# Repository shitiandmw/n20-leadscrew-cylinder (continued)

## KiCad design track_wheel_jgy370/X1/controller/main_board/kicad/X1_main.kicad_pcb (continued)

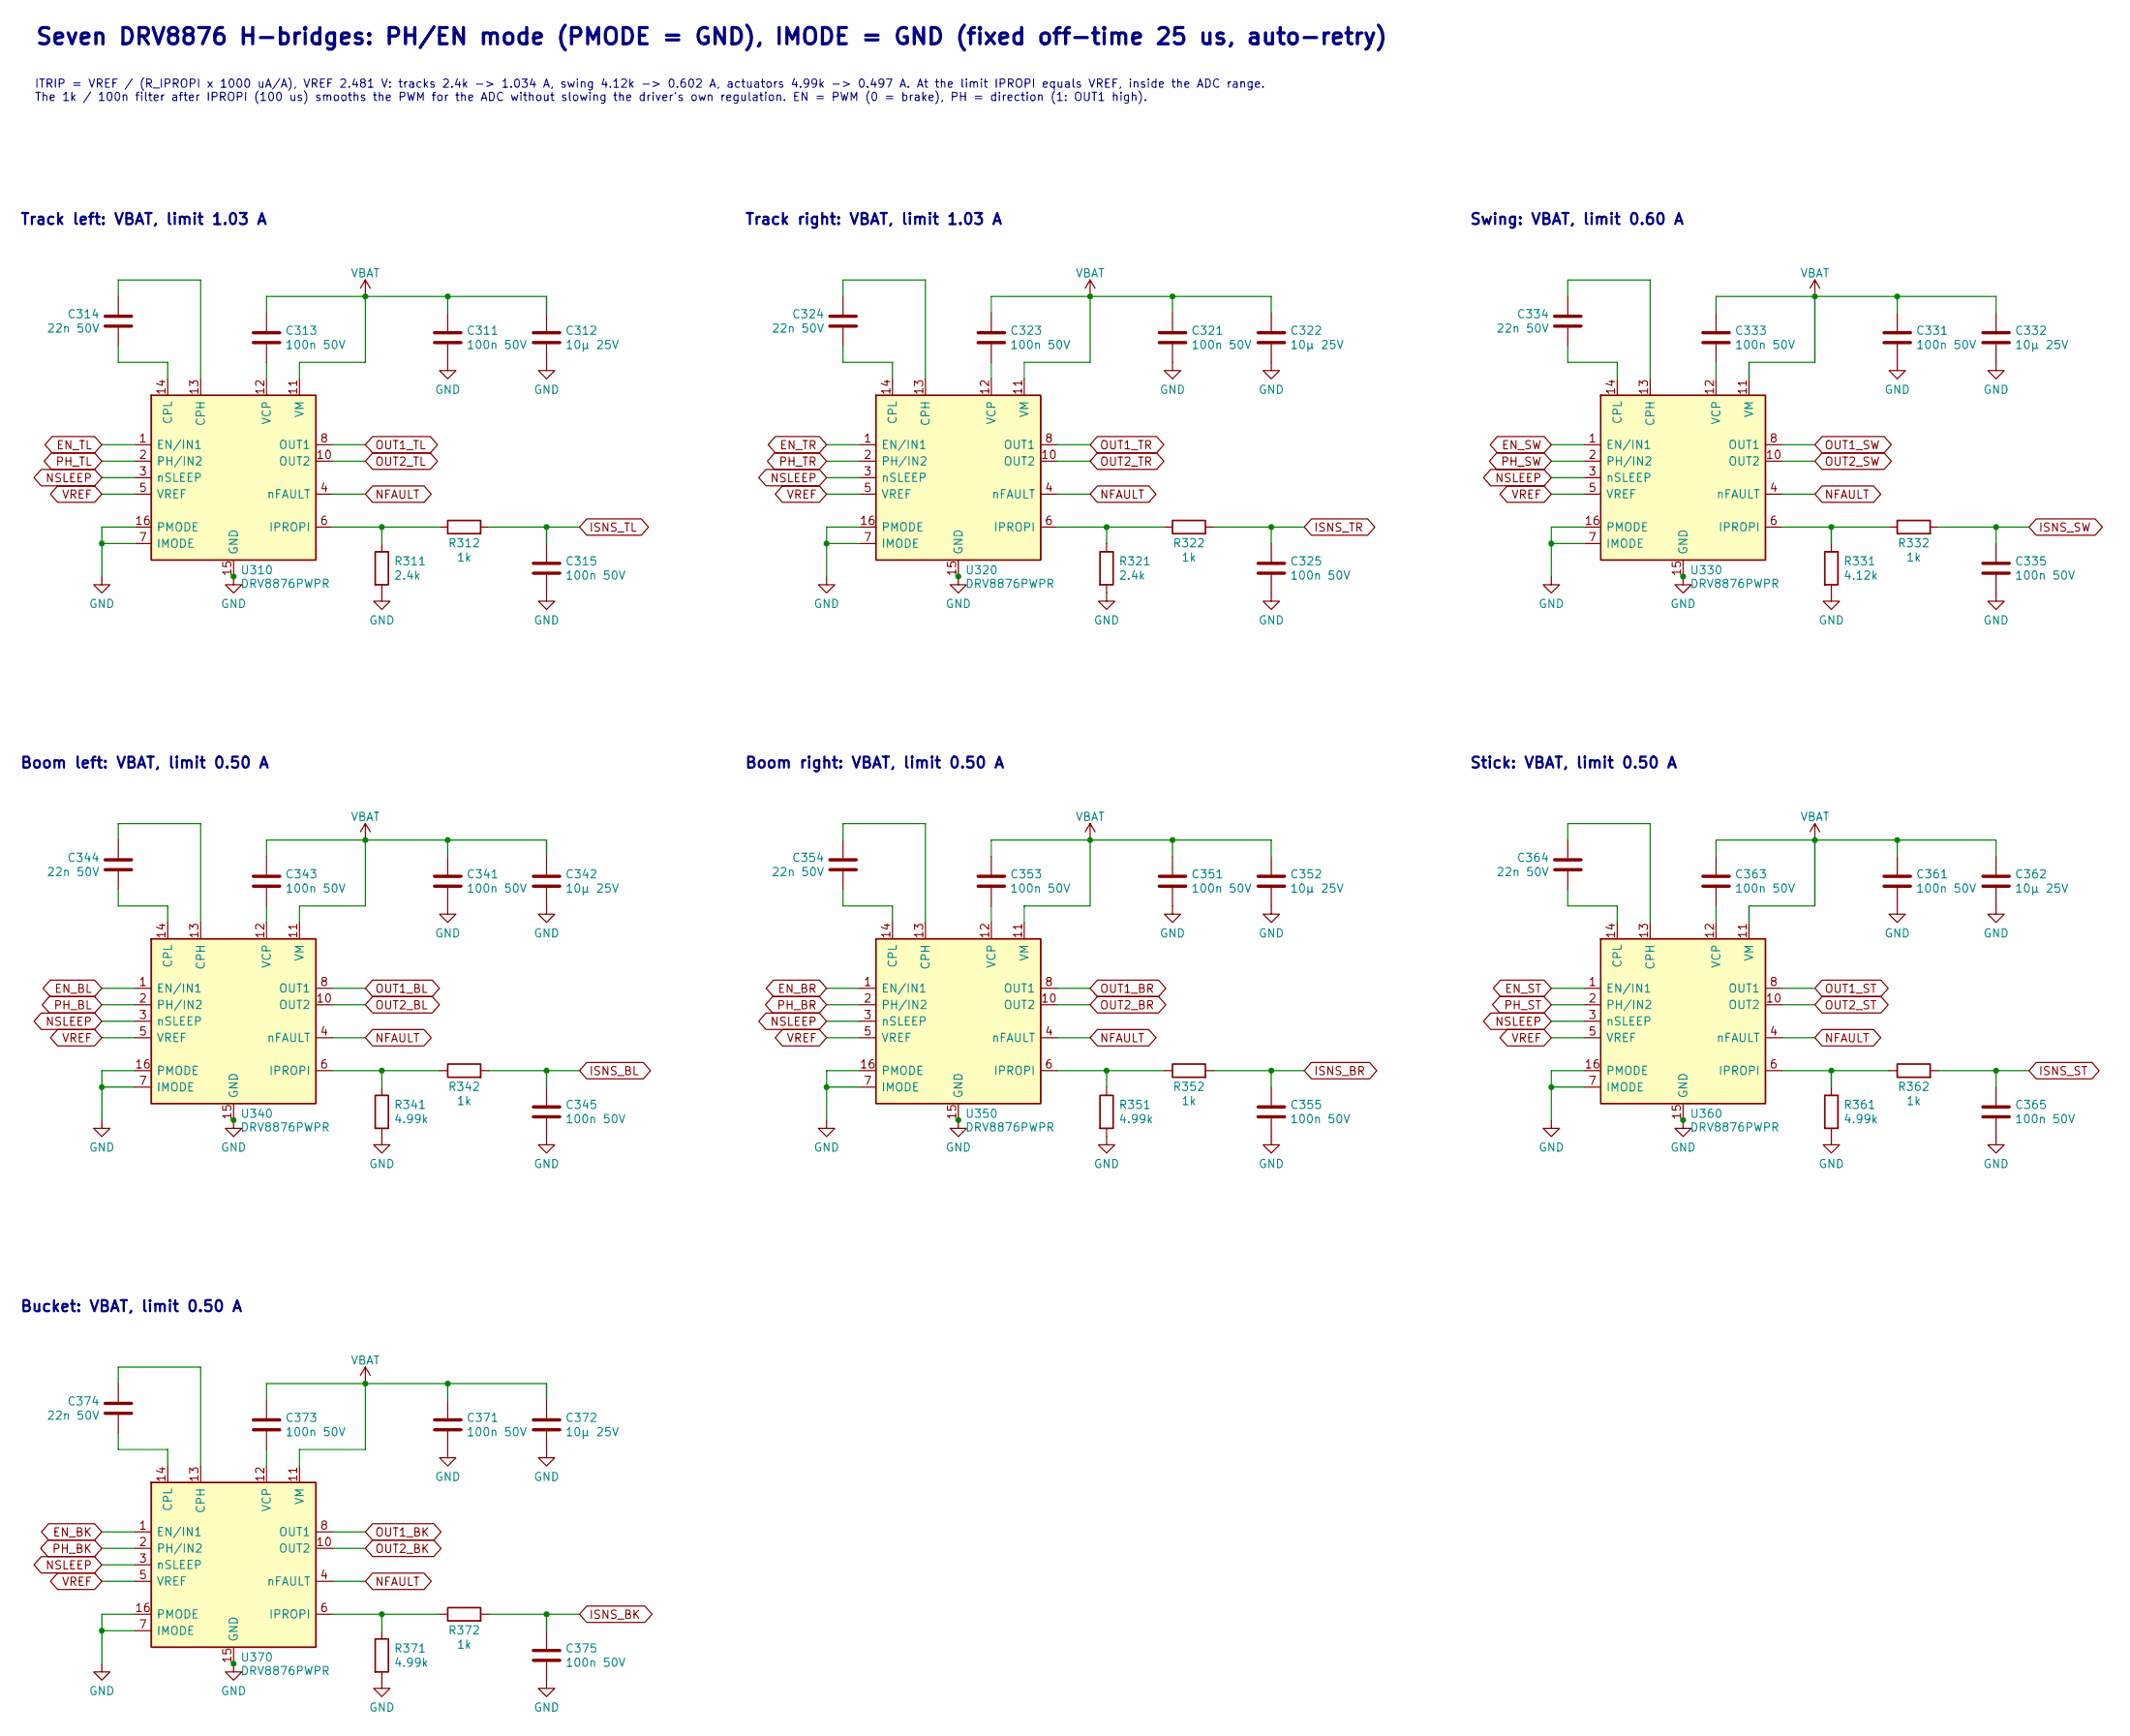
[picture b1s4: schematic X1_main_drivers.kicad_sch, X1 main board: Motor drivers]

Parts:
C311, C313, C315, C321, C323, C325, C331, C333, C335, C341, C343, C345, C351, C353, C355, C361, C363, C365, C371, C373, C375: 100n 50V; C_0603_1608Metric; MPN Yageo CC0603KRX7R9BB104; LCSC C14663
C312, C322, C332, C342, C352, C362, C372: 10µ 25V; C_0805_2012Metric; MPN Samsung CL21A106KAYNNNE; LCSC C15850
C314, C324, C334, C344, C354, C364, C374: 22n 50V; C_0603_1608Metric; MPN Samsung CL10B223KB8NNNC; LCSC C21122
R311, R321: 2.4k; R_0603_1608Metric; MPN UNI-ROYAL 0603WAF, 2.4k 1 %; LCSC C22940
R312, R322, R332, R342, R352, R362, R372: 1k; R_0603_1608Metric; MPN UNI-ROYAL 0603WAF, 1k 1 %; LCSC C21190
R331: 4.12k; R_0603_1608Metric; MPN UNI-ROYAL 0603WAF, 4.12k 1 %; LCSC C23041
R341, R351, R361, R371: 4.99k; R_0603_1608Metric; MPN UNI-ROYAL 0603WAF, 4.99k 1 %; LCSC C23046
U310, U320, U330, U340, U350, U360, U370: DRV8876PWPR; HTSSOP-16-1EP_4.4x5mm_P0.65mm_EP3.4x5mm_Mask2.46x2.31mm_The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; MPN TI DRV8876PWPR; LCSC C575551

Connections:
EN_BK: U370.1 (EN/IN1); also elsewhere on the board
EN_BL: U340.1 (EN/IN1); also elsewhere on the board
EN_BR: U350.1 (EN/IN1); also elsewhere on the board
EN_ST: U360.1 (EN/IN1); also elsewhere on the board
EN_SW: U330.1 (EN/IN1); also elsewhere on the board
EN_TL: U310.1 (EN/IN1); also elsewhere on the board
EN_TR: U320.1 (EN/IN1); also elsewhere on the board
GND: C311.2, C312.2, C315.2, C321.2, C322.2, C325.2, C331.2, C332.2, C335.2, C341.2, C342.2, C345.2, C351.2, C352.2, C355.2, C361.2, C362.2, C365.2, C371.2, C372.2, C375.2, R311.2, R321.2, R331.2, R341.2, R351.2, R361.2, R371.2, U310.7 (IMODE), U310.9 (PGND), U310.15 (GND), U310.16 (PMODE), U310.17 (PAD), U320.7 (IMODE), U320.9 (PGND), U320.15 (GND), U320.16 (PMODE), U320.17 (PAD), U330.7 (IMODE), U330.9 (PGND), U330.15 (GND), U330.16 (PMODE), U330.17 (PAD), U340.7 (IMODE), U340.9 (PGND), U340.15 (GND), U340.16 (PMODE), U340.17 (PAD), U350.7 (IMODE), U350.9 (PGND), U350.15 (GND), U350.16 (PMODE), U350.17 (PAD), U360.7 (IMODE), U360.9 (PGND), U360.15 (GND), U360.16 (PMODE), U360.17 (PAD), U370.7 (IMODE), U370.9 (PGND), U370.15 (GND), U370.16 (PMODE), U370.17 (PAD); also elsewhere on the board
ISNS_BK: C375.1, R372.2; also elsewhere on the board
ISNS_BL: C345.1, R342.2; also elsewhere on the board
ISNS_BR: C355.1, R352.2; also elsewhere on the board
ISNS_ST: C365.1, R362.2; also elsewhere on the board
ISNS_SW: C335.1, R332.2; also elsewhere on the board
ISNS_TL: C315.1, R312.2; also elsewhere on the board
ISNS_TR: C325.1, R322.2; also elsewhere on the board
NFAULT: U310.4 (nFAULT), U320.4 (nFAULT), U330.4 (nFAULT), U340.4 (nFAULT), U350.4 (nFAULT), U360.4 (nFAULT), U370.4 (nFAULT); also elsewhere on the board
NSLEEP: U310.3 (nSLEEP), U320.3 (nSLEEP), U330.3 (nSLEEP), U340.3 (nSLEEP), U350.3 (nSLEEP), U360.3 (nSLEEP), U370.3 (nSLEEP); also elsewhere on the board
unnamed: C314.1, U310.13 (CPH)
unnamed: C314.2, U310.14 (CPL)
unnamed: R311.1, R312.1, U310.6 (IPROPI)
unnamed: C313.1, U310.12 (VCP)
unnamed: C324.1, U320.13 (CPH)
unnamed: C324.2, U320.14 (CPL)
unnamed: R321.1, R322.1, U320.6 (IPROPI)
unnamed: C323.1, U320.12 (VCP)
unnamed: C334.1, U330.13 (CPH)
unnamed: C334.2, U330.14 (CPL)
unnamed: R331.1, R332.1, U330.6 (IPROPI)
unnamed: C333.1, U330.12 (VCP)
unnamed: C344.1, U340.13 (CPH)
unnamed: C344.2, U340.14 (CPL)
unnamed: R341.1, R342.1, U340.6 (IPROPI)
unnamed: C343.1, U340.12 (VCP)
unnamed: C354.1, U350.13 (CPH)
unnamed: C354.2, U350.14 (CPL)
unnamed: R351.1, R352.1, U350.6 (IPROPI)
unnamed: C353.1, U350.12 (VCP)
unnamed: C364.1, U360.13 (CPH)
unnamed: C364.2, U360.14 (CPL)
unnamed: R361.1, R362.1, U360.6 (IPROPI)
unnamed: C363.1, U360.12 (VCP)
unnamed: C374.1, U370.13 (CPH)
unnamed: C374.2, U370.14 (CPL)
unnamed: R371.1, R372.1, U370.6 (IPROPI)
unnamed: C373.1, U370.12 (VCP)
OUT1_BK: U370.8 (OUT1); also elsewhere on the board
OUT1_BL: U340.8 (OUT1); also elsewhere on the board
OUT1_BR: U350.8 (OUT1); also elsewhere on the board
OUT1_ST: U360.8 (OUT1); also elsewhere on the board
OUT1_SW: U330.8 (OUT1); also elsewhere on the board
OUT1_TL: U310.8 (OUT1); also elsewhere on the board
OUT1_TR: U320.8 (OUT1); also elsewhere on the board
OUT2_BK: U370.10 (OUT2); also elsewhere on the board
OUT2_BL: U340.10 (OUT2); also elsewhere on the board
OUT2_BR: U350.10 (OUT2); also elsewhere on the board
OUT2_ST: U360.10 (OUT2); also elsewhere on the board
OUT2_SW: U330.10 (OUT2); also elsewhere on the board
OUT2_TL: U310.10 (OUT2); also elsewhere on the board
OUT2_TR: U320.10 (OUT2); also elsewhere on the board
PH_BK: U370.2 (PH/IN2); also elsewhere on the board
PH_BL: U340.2 (PH/IN2); also elsewhere on the board
PH_BR: U350.2 (PH/IN2); also elsewhere on the board
PH_ST: U360.2 (PH/IN2); also elsewhere on the board
PH_SW: U330.2 (PH/IN2); also elsewhere on the board
PH_TL: U310.2 (PH/IN2); also elsewhere on the board
PH_TR: U320.2 (PH/IN2); also elsewhere on the board
VBAT: C311.1, C312.1, C313.2, C321.1, C322.1, C323.2, C331.1, C332.1, C333.2, C341.1, C342.1, C343.2, C351.1, C352.1, C353.2, C361.1, C362.1, C363.2, C371.1, C372.1, C373.2, U310.11 (VM), U320.11 (VM), U330.11 (VM), U340.11 (VM), U350.11 (VM), U360.11 (VM), U370.11 (VM); also elsewhere on the board
VREF: U310.5 (VREF), U320.5 (VREF), U330.5 (VREF), U340.5 (VREF), U350.5 (VREF), U360.5 (VREF), U370.5 (VREF); also elsewhere on the board

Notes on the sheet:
Seven DRV8876 H-bridges: PH/EN mode (PMODE = GND), IMODE = GND (fixed off-time 25 us, auto-retry)
ITRIP = VREF / (R_IPROPI x 1000 uA/A), VREF 2.481 V: tracks 2.4k -> 1.034 A, swing 4.12k -> 0.602 A, actuators 4.99k -> 0.497 A. At the limit IPROPI equals VREF, inside the ADC range. The 1k / 100n filter after IPROPI (100 us) smooths the PWM for the ADC without slowing the driver's own regulation.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
Track left: VBAT, limit 1.03 A
Track right: VBAT, limit 1.03 A
Swing: VBAT, limit 0.60 A
Boom left: VBAT, limit 0.50 A
Boom right: VBAT, limit 0.50 A
Stick: VBAT, limit 0.50 A
Bucket: VBAT, limit 0.50 A

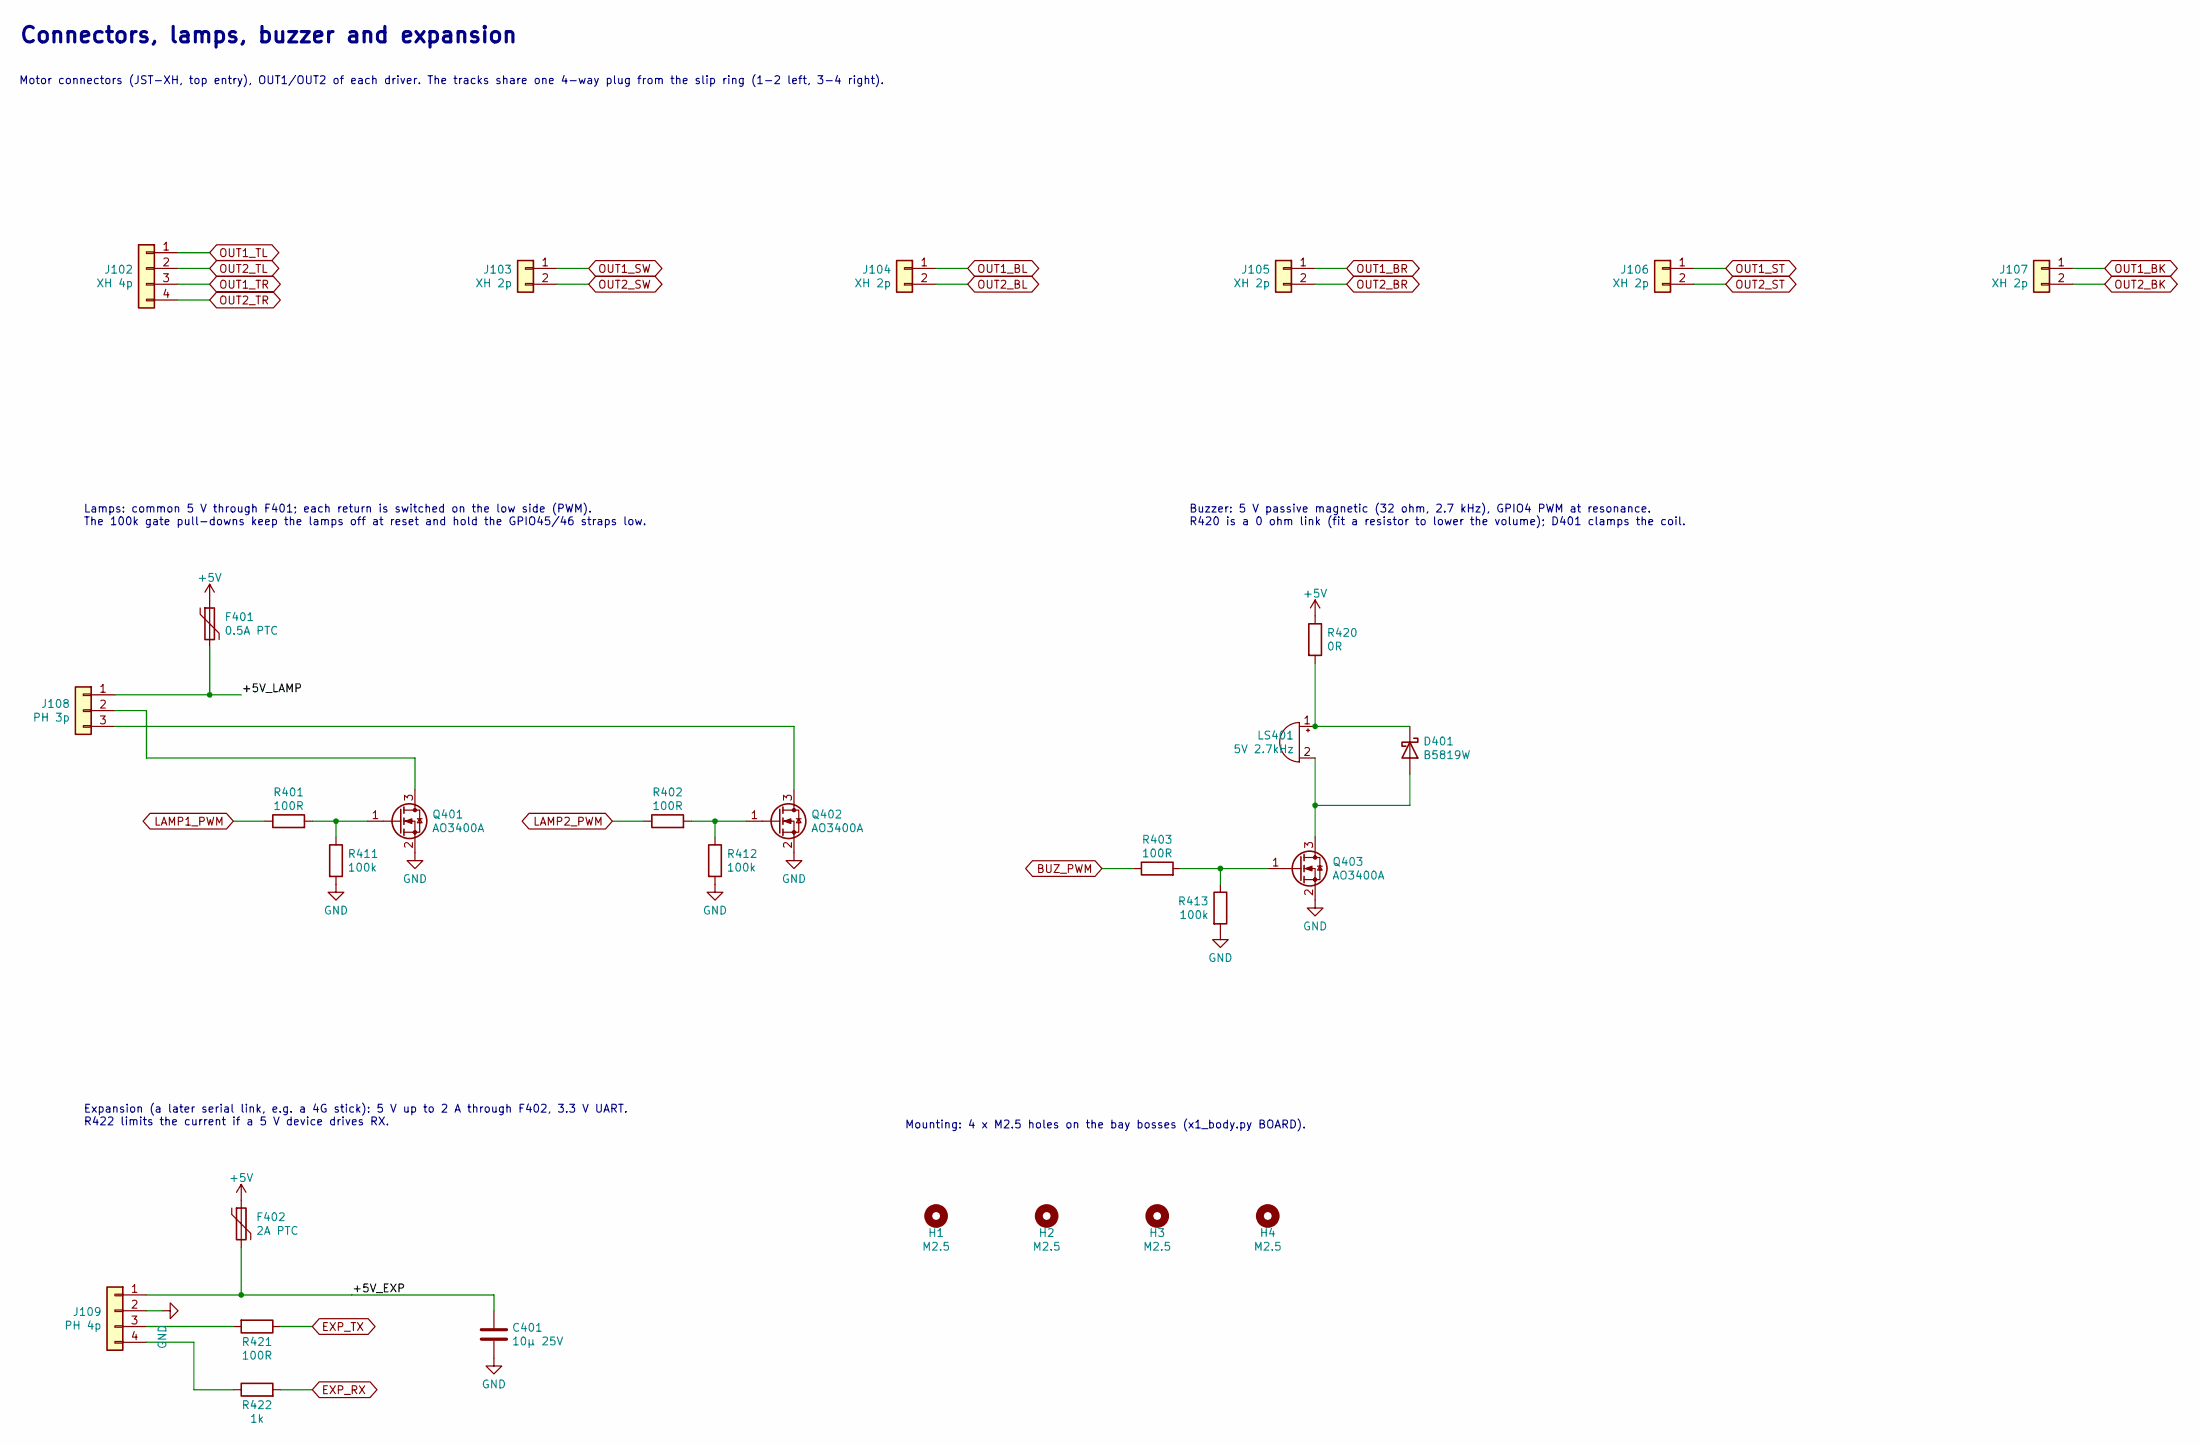
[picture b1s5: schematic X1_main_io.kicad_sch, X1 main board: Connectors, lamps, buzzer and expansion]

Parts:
C401: 10µ 25V; C_0805_2012Metric; MPN Samsung CL21A106KAYNNNE; LCSC C15850
D401: B5819W; D_SOD-123; MPN JSCJ B5819W SL; LCSC C8598
F401: 0.5A PTC; Fuse_1206_3216Metric; MPN BHFUSE BSMD1206-050-16V; LCSC C883124
F402: 2A PTC; Fuse_1812_4532Metric; MPN BHFUSE BSMD1812-200-16V; LCSC C883156
H1, H2, H3, H4: M2.5; MountingHole_2.7mm_M2.5; MPN mounting hole
J102: XH 4p; JST_XH_B4B-XH-A_1x04_P2.50mm_Vertical; MPN JST B4B-XH-A(LF)(SN); LCSC C144395
J103, J104, J105, J106, J107: XH 2p; JST_XH_B2B-XH-A_1x02_P2.50mm_Vertical; MPN JST B2B-XH-A(LF)(SN); LCSC C158012
J108: PH 3p; JST_PH_B3B-PH-K_1x03_P2.00mm_Vertical; MPN JST B3B-PH-K-S(LF)(SN); LCSC C131339
J109: PH 4p; JST_PH_B4B-PH-K_1x04_P2.00mm_Vertical; MPN JST B4B-PH-K-S(LF)(SN); LCSC C131334
LS401: 5V 2.7kHz; Buzzer_XHXDZ_8530; MPN XHXDZ SMD8530-32Ω (5 V passive, 32 Ω); LCSC C49246949
Q401, Q402, Q403: AO3400A; SOT-23; MPN AOS AO3400A; LCSC C20917
R401, R402, R403, R421: 100R; R_0603_1608Metric; MPN UNI-ROYAL 0603WAF, 100R 1 %; LCSC C22775
R411, R412, R413: 100k; R_0603_1608Metric; MPN UNI-ROYAL 0603WAF, 100k 1 %; LCSC C25803
R420: 0R; R_0603_1608Metric; MPN UNI-ROYAL 0603WAF, 0R 1 %; LCSC C21189
R422: 1k; R_0603_1608Metric; MPN UNI-ROYAL 0603WAF, 1k 1 %; LCSC C21190

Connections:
+5V: F401.1, F402.1, R420.1; also elsewhere on the board
/Connectors, lamps, buzzer and expansion/+5V_EXP: C401.1, F402.2, J109.1
/Connectors, lamps, buzzer and expansion/+5V_LAMP: F401.2, J108.1
BUZ_PWM: R403.1; also elsewhere on the board
EXP_RX: R422.2; also elsewhere on the board
EXP_TX: R421.1; also elsewhere on the board
GND: C401.2, J109.2, Q401.2 (S), Q402.2 (S), Q403.2 (S), R411.2, R412.2, R413.2; also elsewhere on the board
LAMP1_PWM: R401.1; also elsewhere on the board
LAMP2_PWM: R402.1; also elsewhere on the board
unnamed: D401.2 (A), LS401.2 (-), Q403.3 (D)
unnamed: D401.1 (K), LS401.1 (+), R420.2
unnamed: J108.2, Q401.3 (D)
unnamed: J108.3, Q402.3 (D)
unnamed: J109.3, R421.2
unnamed: J109.4, R422.1
unnamed: Q401.1 (G), R401.2, R411.1
unnamed: Q402.1 (G), R402.2, R412.1
unnamed: Q403.1 (G), R403.2, R413.1
OUT1_BK: J107.1; also elsewhere on the board
OUT1_BL: J104.1; also elsewhere on the board
OUT1_BR: J105.1; also elsewhere on the board
OUT1_ST: J106.1; also elsewhere on the board
OUT1_SW: J103.1; also elsewhere on the board
OUT1_TL: J102.1; also elsewhere on the board
OUT1_TR: J102.3; also elsewhere on the board
OUT2_BK: J107.2; also elsewhere on the board
OUT2_BL: J104.2; also elsewhere on the board
OUT2_BR: J105.2; also elsewhere on the board
OUT2_ST: J106.2; also elsewhere on the board
OUT2_SW: J103.2; also elsewhere on the board
OUT2_TL: J102.2; also elsewhere on the board
OUT2_TR: J102.4; also elsewhere on the board

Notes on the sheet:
Connectors, lamps, buzzer and expansion
Motor connectors (JST-XH, top entry), OUT1/OUT2 of each driver. The tracks share one 4-way plug from the slip ring (1-2 left, 3-4 right).
Lamps: common 5 V through F401; each return is switched on the low side (PWM). The 100k gate pull-downs keep the lamps off at reset and hold the GPIO45/46 straps low.
Buzzer: 5 V passive magnetic (32 ohm, 2.7 kHz), GPIO4 PWM at resonance. R420 is a 0 ohm link (fit a resistor to lower the volume); D401 clamps the coil.
Expansion (a later serial link, e.g. a 4G stick): 5 V up to 2 A through F402, 3.3 V UART. R422 limits the current if a 5 V device drives RX.
Mounting: 4 x M2.5 holes on the bay bosses (x1_body.py BOARD).

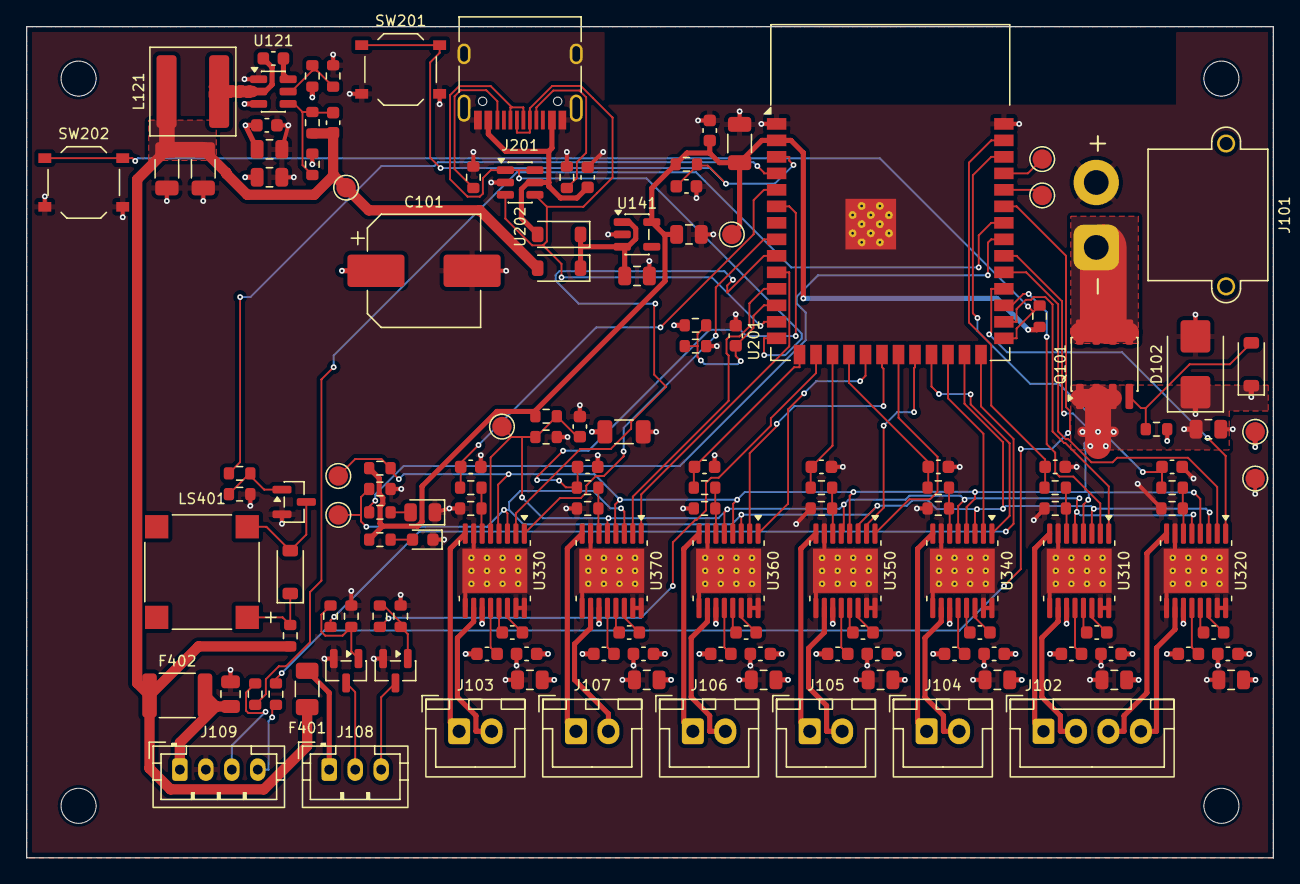
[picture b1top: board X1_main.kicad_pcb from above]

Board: 4 copper layers, 96.0 x 64.0 mm, 145 parts (0 on the bottom side), 106 nets.

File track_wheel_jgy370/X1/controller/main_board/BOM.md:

# X1 main board rev B: bill of materials

Generated by `source/bom.py` from `source/netlist.py`; do not edit by hand.

- 42 lines and 132 placed parts per board. Test pads and mounting holes are copper only.
- **JLCPCB library type:** 19 lines are Basic, 1 are Preferred Extended, and 22 are Extended, which carry a per-part loading fee.
- The library type, part numbers and ratings were checked on LCSC and JLCPCB on 2026-11-05 (sources in DESIGN.md).

| Designators | Qty | Value | Part | Footprint | LCSC | JLC library | Height mm |
|---|---|---|---|---|---|---|---|
| C101 | 1 | 220µ 35V | Nichicon UCD1V221MNL1GS | `CP_Elec_8x10.5` | C136294 | Extended | 10.5 |
| C102, C121, C122, C141, C142, C312, C322, C332, C342, C352, C362, C372, C401 | 13 | 10µ 25V | Samsung CL21A106KAYNNNE | `C_0805_2012Metric` | C15850 | Basic | 1.25 |
| C103, C123, C124, C151, C202, C311, C313, C315, C321, C323, C325, C331, C333, C335, C341, C343, C345, C351, C353, C355, C361, C363, C365, C371, C373, C375 | 26 | 100n 50V | Yageo CC0603KRX7R9BB104 | `C_0603_1608Metric` | C14663 | Basic | 0.9 |
| C125, C126, C130, C201 | 4 | 22µ 25V | Samsung CL31A226KAHNNNE | `C_1206_3216Metric` | C12891 | Basic | 1.6 |
| C127 | 1 | 68p C0G | Samsung CL10C680JB8NNNC | `C_0603_1608Metric` | C28262 | Preferred ext. | 0.9 |
| C203, C204 | 2 | 1µ 50V | Samsung CL10A105KB8NNNC | `C_0603_1608Metric` | C15849 | Basic | 0.9 |
| C314, C324, C334, C344, C354, C364, C374 | 7 | 22n 50V | Samsung CL10B223KB8NNNC | `C_0603_1608Metric` | C21122 | Basic | 0.9 |
| D101 | 1 | BZT52C12 | JSCJ BZT52C12 | `D_SOD-123` | C43491 | Extended | 1.35 |
| D102 | 1 | SMBJ15A | Littelfuse SMBJ15A (unidirectional) | `D_SMB` | C83846 | Extended | 2.3 |
| D141, D142, D401 | 3 | B5819W | JSCJ B5819W SL | `D_SOD-123` | C8598 | Basic | 1.35 |
| D201 | 1 | green | Hubei KENTO KT-0805G | `LED_0805_2012Metric` | C2297 | Basic | 0.8 |
| D202 | 1 | red | Hubei KENTO KT-0603R | `LED_0603_1608Metric` | C2286 | Basic | 0.8 |
| F401 | 1 | 0.5A PTC | BHFUSE BSMD1206-050-16V | `Fuse_1206_3216Metric` | C883124 | Extended | 1 |
| F402 | 1 | 2A PTC | BHFUSE BSMD1812-200-16V | `Fuse_1812_4532Metric` | C883156 | Extended | 1 |
| J101 | 1 | XT30PW-M | Amass XT30PW-M30.G.Y | `AMASS_XT30PW-M_1x02_P2.50mm_Horizontal` | C431092 | Extended | 5.2 |
| J102 | 1 | XH 4p | JST B4B-XH-A(LF)(SN) | `JST_XH_B4B-XH-A_1x04_P2.50mm_Vertical` | C144395 | Extended | 7 |
| J103, J104, J105, J106, J107 | 5 | XH 2p | JST B2B-XH-A(LF)(SN) | `JST_XH_B2B-XH-A_1x02_P2.50mm_Vertical` | C158012 | Extended | 7 |
| J108 | 1 | PH 3p | JST B3B-PH-K-S(LF)(SN) | `JST_PH_B3B-PH-K_1x03_P2.00mm_Vertical` | C131339 | Extended | 6 |
| J109 | 1 | PH 4p | JST B4B-PH-K-S(LF)(SN) | `JST_PH_B4B-PH-K_1x04_P2.00mm_Vertical` | C131334 | Extended | 6 |
| J201 | 1 | USB-C | Korean Hroparts TYPE-C-31-M-12 | `USB_C_Receptacle_HRO_TYPE-C-31-M-12` | C165948 | Extended | 3.26 |
| L121 | 1 | 10µH | Bourns SRP6060FA-100M | `L_Bourns_SRP6060FA` | C2046759 | Extended | 6 |
| LS401 | 1 | 5V 2.7kHz | XHXDZ SMD8530-32Ω (5 V passive, 32 Ω) | `Buzzer_XHXDZ_8530` | C49246949 | Extended | 3 |
| Q101 | 1 | AO4407A | AOS AO4407A | `SOIC-8_3.9x4.9mm_P1.27mm` | C16072 | Extended | 1.75 |
| Q401, Q402, Q403 | 3 | AO3400A | AOS AO3400A | `SOT-23` | C20917 | Extended | 1.25 |
| R101, R102, R121, R123, R208, R411, R412, R413 | 8 | 100k | UNI-ROYAL 0603WAF, 100k 1 % | `R_0603_1608Metric` | C25803 | Basic | 0.5 |
| R103, R124 | 2 | 22k | UNI-ROYAL 0603WAF, 22k 1 % | `R_0603_1608Metric` | C31850 | Basic | 0.5 |
| R122 | 1 | 13.3k | UNI-ROYAL 0603WAF, 13.3k 1 % | `R_0603_1608Metric` | C25952 | Extended | 0.5 |
| R151 | 1 | 3.3k | UNI-ROYAL 0603WAF, 3.3k 1 % | `R_0603_1608Metric` | C22978 | Basic | 0.5 |
| R152, R201, R202, R207 | 4 | 10k | UNI-ROYAL 0603WAF, 10k 1 % | `R_0603_1608Metric` | C25804 | Basic | 0.5 |
| R203, R204 | 2 | 5.1k | UNI-ROYAL 0603WAF, 5.1k 1 % | `R_0603_1608Metric` | C23186 | Basic | 0.5 |
| R205, R206, R312, R322, R332, R342, R352, R362, R372, R422 | 10 | 1k | UNI-ROYAL 0603WAF, 1k 1 % | `R_0603_1608Metric` | C21190 | Basic | 0.5 |
| R311, R321 | 2 | 2.4k | UNI-ROYAL 0603WAF, 2.4k 1 % | `R_0603_1608Metric` | C22940 | Basic | 0.5 |
| R331 | 1 | 4.12k | UNI-ROYAL 0603WAF, 4.12k 1 % | `R_0603_1608Metric` | C23041 | Extended | 0.5 |
| R341, R351, R361, R371 | 4 | 4.99k | UNI-ROYAL 0603WAF, 4.99k 1 % | `R_0603_1608Metric` | C23046 | Basic | 0.5 |
| R401, R402, R403, R421 | 4 | 100R | UNI-ROYAL 0603WAF, 100R 1 % | `R_0603_1608Metric` | C22775 | Basic | 0.5 |
| R420 | 1 | 0R | UNI-ROYAL 0603WAF, 0R 1 % | `R_0603_1608Metric` | C21189 | Basic | 0.5 |
| SW201, SW202 | 2 | SW_Push | XKB TS-1187A-B-A-B | `SW_Push_1P1T_XKB_TS-1187A` | C318884 | Basic | 1.5 |
| U121 | 1 | TPS54302DDCR | TI TPS54302DDCR | `SOT-23-6` | C311983 | Extended | 1.1 |
| U141 | 1 | AP2112K-3.3 | Diodes AP2112K-3.3TRG1 | `SOT-23-5` | C51118 | Extended | 1.45 |
| U201 | 1 | ESP32-S3-WROOM-1-N8 | Espressif ESP32-S3-WROOM-1-N8 | `ESP32-S3-WROOM-1_X1` | C2913198 | Extended | 3.1 |
| U202 | 1 | USBLC6-2SC6 | ST USBLC6-2SC6 | `SOT-23-6` | C7519 | Extended | 1.45 |
| U310, U320, U330, U340, U350, U360, U370 | 7 | DRV8876PWPR | TI DRV8876PWPR | `HTSSOP-16-1EP_4.4x5mm_P0.65mm_EP3.4x5mm_Mask2.46x2.31mm_ThermalVias` | C575551 | Extended | 1.2 |

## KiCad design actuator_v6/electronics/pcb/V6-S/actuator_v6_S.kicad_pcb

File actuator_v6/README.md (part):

# V6 two-wire leadscrew actuator

A general-purpose linear actuator built around the N20 gearmotor with its own leadscrew: since rev 6.2 the 12 V, 1:50, 800 rpm motor with an M4 × 0.7 screw.

The [motor gear update](MOTOR_UPDATE.md) replaces the internal motor model in all three lengths with the supplied meshed gearbox. Open **Motor gears** in the [offline preview](3D_preview.html) to inspect the three stages and their motion.

- **Control:** two wires. The polarity sets the direction, a Hall switch at each end stops the rod by itself, and reversing always drives it back out.
- **Construction:** every custom part is printed in PETG and held together with standard screws.
- **Electronics:** the end-stop circuit sits on a small board inside the body. It has 17 parts and no microcontroller.

Three lengths share every part except the body, the rod, the board and the length of the motor's leadscrew (cut from the motor's 100 mm screw):

| Version | Leadscrew | Stroke |
|---|---|---|
| **V6-S** | 55 mm | 40 mm |
| **V6-U60** | 75 mm | 60 mm |
| **V6-L** | 100 mm | 85 mm |

V6-U60 is also the common actuator of the 60 mm excavator arm in `../excavator_arm_60mm/`, which uses four of them. The arm's `source/build_actuators.py` builds V6-U60 here and checks it against the arm's kinematics.

This folder holds the **partition revision**. It adds a continuous **1.00 mm printed PETG wall between the moving carrier and the PCB components**.
- **Construction:** the partition is part of `01_body`, not a separate insert. It runs from the motor mounting wall to the front of the body and covers the whole circuit compartment.
- **Sensing:** the Hall switches see the magnet through the plastic; there are no openings in the wall.
- **Provenance:** this revision was generated in checkout `14c0f3ad` on 28 October 2026 and replaced the earlier V6 files in this folder.

| V6-S | V6-U60 | V6-L |
|---|---|---|
|  |  |  |

## Rod-eye screw threads into the rod, 15 November 2026

- **Why:** the M2 × 10 cross screw used to cut its thread in the rod eye's far wall. That wall is only 1.45 mm thick (Ø11 eye on a Ø8.1 socket), so the screw held by 1.35 mm of thread, about 3½ turns in printed PETG, and stripped easily when tightened.
- **Now:** the Ø1.7 mm hole goes straight through the solid Ø8 rod, and the screw cuts about 7.9 mm of thread there (about 20 turns). Both eye walls have Ø2.2 mm clearance holes and bear on the screw like a pin; the head still sits in the Ø4 counterbore, and the tip stops 0.1 mm short of the eye's outside. Same screw, outline and assembly step.
- **Loads, unchanged:** the screw carries only pull (retracting under load); a push goes from the rod's end face onto the socket bottom. The thread only has to keep the screw in.
- **Why no heat-set insert:** an M2 insert does not fit the eye's 1.45 mm wall (an M2 × 3 × 3.2 would stick 1.55 mm into the socket). One fits in the rod, but the melt it pushes up at the hole mouth would have to be trimmed flush, because the rod is a 0.05 mm sliding fit in the socket. The cut thread is ample for this screw.
- **Checked in CAD** (`validation.json`, all three lengths): the screw's only overlap is its thread in `04_rod` (an intended overlap); it is clear of `05_rod_eye`.
- **Changed prints:** `04_rod` (13 mm³ more PETG) and `05_rod_eye` (2 mm³ less), both on plate 3. Print them together: a rod printed before this change has a Ø2.2 hole, which leaves the screw nothing to grip in a new eye.
- **Step 8.4 clarified:** keep B positive (W2 black to +) on until the rod stops by itself, 5–10 s depending on the length. The front Hall switch may see the magnet at the start, but it only stops extending.
- **Pictures:** the 3D preview and its **Assembly ▶** animation carry the new captions. The assembly video `images/assembly_V6-S.mp4` was not re-recorded: its step 14 caption still says that the screw threads into the far wall.

## Front cap held on the motor side too, 14 November 2026

The front cap's two screws sat on the board side only, like the rear cap's before its hook. The front cap takes load only if the carrier runs past the front Hall stop into its spigot, for example if U2 does not switch. At the X1 board's 0.5 A limit that push is about 85 N. It tipped the cap about the body's board-side edge, and each screw carried about 1.9× the push: 158 N, above the inserts' estimated 100–150 N pull-out. Now **a third M1 screw holds the motor side**.

- **Why not a hook like the rear cap's:** the front cap is threaded onto the rod, and its spigot and board tongue sit in the body with 0.075–0.20 mm of play, so it can only go straight on. The body also prints front end down, so nothing may stand out of its front face.
- **Where:** the key rib in the bore's motor-side corner makes that corner the only thick spot on the motor side. The rib grew from 2.0 to 2.5 mm, and the third insert sits at (−5.76, −5.56) with **0.78 mm of PETG round its knurl** (1.78× the knurl; the two board-side front inserts have 0.70 mm). The rod still goes in one way round only.
- **The rib now reaches the front face:** the bore's 0.3 mm lead-in used to cut the rib off in its last 0.3 mm, which would have opened the new hole into the bore at the face. The lead-in now follows the rib's face with a 0.3 mm 45° chamfer of its own, and leaves 0.56 mm of wall round the hole at the face. `cap_inserts` now measures that wall at every insert hole; the board-side front ones have 0.47 mm there.
- **Loads at a jam:** the push now sits inside the screws' triangle. The most loaded screw carries 0.52× the push: 44 N at 85 N, and 29 N at the 55 N rating (158 N and 102 N before). These are estimates, with a rigid cap on the body's face and the screws as equal springs.
- **Checked in CAD** (`validation.json`, all three lengths; every check passes):
  - `cap_inserts`: 0.78 mm of PETG round the new knurl and 0.56 mm of wall round its hole at the face; the screw runs through its whole insert and stops 0.5 mm short of the hole bottom, like the others;
  - tool access: the soldering iron reaches the new insert, and the PH000 driver the new screw, without touching anything fitted before; the driver passes 0.71 mm from the cap and 2.76 mm from the rod;
  - a rod turned 180° overlaps the bigger rib by 23 mm³ (13 mm³ before), so it still goes in one way round only;
  - the assembly has no overlaps at any sampled travel position.
- **Parts:** five inserts and five M1 × 8 per actuator, one more of each (`ASSEMBLY.md` steps 3 and 9).
- **Changed prints:** `01_body` (the rib and the third hole, 0.1 g heavier), `02_front_cap` (the third screw hole and head pocket), `04_rod` (its carrier's corner keeps its 0.2 mm from the bigger rib), and fit samples 08, 09 and 11. Sample 11 now has the third hole and the rib: after pressing the inserts in, slide sample 09 through it. The outline, pins, strokes and lengths are unchanged, so the arms fit as before.
- **Not compatible:** rods and front caps printed before this change jam on the bigger rib of a new body.
- **Pictures:** the 3D preview and its **Assembly ▶** animation show the third insert and screw. The assembly video `images/assembly_V6-S.mp4` was not re-recorded (about 2 h of software rendering): it shows two front inserts and two front screws.

## Parts showcase and print plates for four V6-U60, 14 November 2026

For the R12 arm's four drives:
- **`parts_showcase.html`:** every part to print and to buy, and the tools, in 3D. A printed part is shown on the print bed or as fitted, can be cut open, and has its dimensions drawn on the model, with its settings and its plate. The bought parts come from the CAD. "In the actuator" and "Cut open" show where each part sits. The page works offline.
- **`print_plates/`:** the printed parts of four V6-U60 on four plates for a 180 × 180 mm bed, as PrusaSlicer 3MF files that carry each part's settings, and as STL. Plate 1 is the fit test. `print_plates/PRINT_PLATES.md` lists the plates, their settings and PrusaSlicer 2.9.2's estimate: 105 g of PETG and about 20 hours in all.
- **Checks:** every dimension drawn in the showcase was checked against the part's mesh when the page was built (`parts_showcase_report.json`). A headless-browser run checked the page against `BOM.md`, `ASSEMBLY.md`, the plate files and the STL files (`parts_showcase_browser.json`). The plates hold exactly the released STL files, moved but not turned, at least 6 mm apart and 10 mm inside the bed (`print_plates/V6-U60_x4/plates.json`).

## Rear cap hooked on the motor side, 11 November 2026

The rear cap's two screws sit on the board side only, so a pull used to tip the cap about the body's edge, and each screw carried 2.5–3.4× the pull (see the next section). Now **the end of the motor-side wall hooks the cap**. The structure is the user's own design.

- **Shape:**
  - The motor-side (−X) wall is now 2.4 mm thick instead of 1.2 mm.
  - Its end reaches 1.6 mm beyond the rear face into a 1.9 mm pocket in the rear cap, along the flat part of the wall (10.9 mm).
  - A 45° tooth on the cap sits in a 0.6 mm notch cut into the inside of the wall end. Nothing stands in the motor bay, so the motor still goes in from the rear.
- **Printable profile:** there are no knife edges and no sharp inside V.
  - The tooth has a flat tip with 0.15 mm of room under it, and a 0.2 mm chamfer where it meets the print bed.
  - The notch has an r 0.2 inside corner, and the wall end has a 0.6 mm flat.
  - There is 0.15 mm beside the wall end and 0.3 mm behind it, because the pocket's roof prints as a bridge and may sag.
  - The bevels touch only on their middle 0.45 mm. The first, pointed version (0.6 mm triangles) was dropped as too sharp to print true.
- **Fitting:** set the cap on 0.8 mm toward the board side, so the wall end goes into the pocket, then slide it back. The tooth drops into the notch and the screw holes line up. The two screws then stop the cap sliding out (`ASSEMBLY.md` step 7).
- **Loads at the X1 board's 0.5 A limit (a pull of about 85 N):**
  - the hook takes about 0.58 of the pull;
  - each screw takes about 0.21, about 18 N, against 210–290 N before;
  - the wall has 1.8 mm left at the notch, where a beam estimate gives about 16 MPa. Printed PETG holds roughly 30 MPa across its layers.
  
  These are estimates; the hook has not been pull-tested.
- **Printing:**
  - The wall end stands out of the rear face, so **the body now prints front end down** (before, rear end down). The motor wall is still a bridge, but the motor seat is now its top face; the M1.6 countersinks and the board rest are on its underside.
  - 0.3 mm lead-ins at the bore and board-slot mouths take the first layer's squash on the bed.
  - The rear cap still prints flat face down without support.
- **Checked in CAD** (`validation.json`, `rear_hook`, all three lengths):
  - the tooth catches the wall when the cap is pulled 0.05 mm, and wedges if it is pushed toward the motor side;
  - the four clearances are as drawn;
  - the cap goes on along its fitting path without touching anything already fitted;
  - the motor's way in from the rear is clear.
- **Outside:** the body section is 17.30 × 14.70 mm (16.10 × 14.70 before); the end caps follow it. The pins, strokes and lengths are unchanged. In the R12 arm the 3D clash check still passes with no contact, and its closest gaps (1.10 and 1.32 mm) are unchanged. In the side view, the stick drive's body now clears the boom nose by 1.88 mm (3.05 mm before; 1.0 mm required).
- **Fit sample:** `10_fit_insert_rear` now includes the wall end with its notch, so you can try the rear cap on it.
- **Not compatible:** bodies and caps printed before this change do not fit the new ones.
- **Pictures:** the 3D preview shows the hook, and its **Assembly ▶** animation fits the rear cap in the two moves of step 7.4. The assembly video `images/assembly_V6-S.mp4` and the two `assembly_motor_screws` pictures taken from it were recorded before the hook: they show the thinner motor-side wall, and the video puts the rear cap straight on. They were not re-recorded (about 2 h of software rendering). The Blender renders in `images/` do not show the hook either.

## End caps on M1 heat-set inserts, 11 November 2026

Each end cap is now held by **two M1 × 8 screws in brass heat-set inserts**. Before, M2 screws cut their own thread in the body's corners, but an M2 thread there left only 0.6 mm of PETG to the side face: too thin to tap or self-tap without splitting the layers.

- **Inserts:** M1 × 0.25, 1.8 mm long and 2.0 mm across the knurl (sold as M1 × 1.8 × 2), four per actuator. A soldering iron presses them into Ø1.7 mm holes in the body's end faces before anything else goes in (`ASSEMBLY.md` step 3).
- **Holes moved to the thickest part of each corner**, measured on the body section:
  - **rear end, (7.45, ±5.30):** 1.05 mm of PETG round the knurl. Behind the motor wall there is no board groove, so the corner is 4.1 mm tall;
  - **front end, (6.85, ±5.65):** 0.70 mm. The board groove runs out to the front face and limits the corner there;
  - insert makers ask for a boss of at least 1.5×, ideally 2×, the knurl diameter: 2.05× at the rear, 1.70× at the front.
- **Screws:** M1 × 8 pan head, A2-70 stainless, PH000. Each runs through its whole insert and 1.1 mm beyond it. The heads sit in Ø2.6 mm pockets inside the outline; the old M2 heads stood 0.3 mm proud of the side faces.
- **Loads (corrected on 11 November):** only the two rear screws carry the actuator's pull, and they carry it off-centre.
  - **Why:** the rear pin pulls on the centre line, 7.45 mm from the screws. The cap's other (−X) side is not fastened, so a pull tips the cap about its +X edge, 1.9 mm beyond the screws, like a lever.
  - **Screw load:** each rear screw carries at least 2.5× the pull, and about 3.4× if the contact spreads over that edge:
    - 45–63 N at the R12 stick's largest pull (18 N);
    - 135–190 N at the 55 N rating;
    - 210–290 N at the X1 board's 0.5 A limit (about 85 N).
  - **Limits:** an A2-70 M1 screw yields at about 207 N. The inserts' pull-out from PETG is not tested; about 100–150 N each is estimated. At the screw line the cap bends at about 0.5 MPa per newton of pull, 29 MPa at 55 N.
  - **What it meant:** the joint suited the R12 arm's pulls but not the full 55 N rating in pull. The earlier M2 design had the same lever, at 3.5× or more. The hook added the same day takes most of the pull now (see above).
  - **Other cases:** a push presses the cap onto the end face and does not load the screws. The front cap only takes load if the rod runs past the Hall stop into it.

- **Fit samples:** `10_fit_insert_rear` and `11_fit_insert_front`, the last 5 mm of each end, try the hole size and the insert before you print a body.
- **Pictures:** the 3D preview, the assembly video (now 2 min, with the soldering iron) and the `assembly_motor_screws` pictures show the inserts and the new step numbers. The Blender renders in `images/` still show the old M2 cap screws.
- **Unchanged:** the outside, the pins and the strokes, so the arms fit as before; the rod-eye cross screw is still an M2 × 10.
- **Not compatible:** bodies printed before this change have M2 pilot holes in the old places and do not fit the new caps.

## 12 V motor and M4 leadscrew, 10 November 2026 (rev 6.2)

The motor is now the **12 V N20 gearmotor, 1:50, 800 rpm without load, with an M4 × 0.7 leadscrew**. Its screw comes 100 mm long: cut it to 55 mm for V6-S and 75 mm for V6-U60; V6-L uses it uncut. The outside of the actuator, its pins and its strokes are unchanged, so the arms that use it fit as before.

- **Mechanics:**
  - the rod bore and the motor-wall hole are Ø4.8 for the M4 screw;
  - the carrier takes an M4 thin brass nut (ISO 4035, 7 mm across flats × 2.2 mm);
  - the magnet is an N35 block 3 × 2 × 2 mm, because the Ø3 × 2 cylinder has no room beside an M4 screw;
  - each Hall switch sits 5.10 mm beyond the magnet's end position.
- **Board (rev 6.2), re-rated for 12 V:**
  - Q1 and Q2 are IRLML0060 (60 V, ±16 V gate);
  - D3 is an SMF15CA (15 V stand-off);
  - F1 is an MF-NSMF035X-2 (0.35 A hold, 16 V);
  - new R3 and R4 (220 Ω) in series with D1 and D2 keep the Hall supply's rise far below the DRV5033's 2 V/µs limit.

  It has 17 parts and 10 part numbers, and the boards are 0.2 mm shorter.
- **Simulated at 12.6 V, all nine cases pass:**
  - 6.9 mm/s lifting 49 N;
  - a jam (about 1 A) trips F1 in 1.7 s;
  - the Hall supply rises at most 0.04 V/µs;
  - the rod overshoots an end stop by at most 0.04 mm;
  - the MOSFETs and Schottky diodes see at most 31.5 V, just under the 32 V limit (80 % of the B5819WS's 40 V rating; the MOSFETs are 60 V parts).
- **Not updated:** the Blender renders in `images/` still show the M3 screw, the cylinder magnet and the earlier board parts (no Blender here). The outside is unchanged. The 3D preview, the assembly video `images/assembly_V6-S.mp4` and the two `assembly_motor_screws` pictures taken from it (re-recorded on 11 November), the STEP and STL files and the board images are current.
- **Measure before printing:** no seller drawing of the M4 version was found. The model assumes the standard N20 gearbox face with the Ø4 bushing that the seller's photos show, and the M4 thread starting just in front of it (0.1 mm clear of the bushing face).

## Enclosure revision, 29 October 2026

The housing was reworked so that it is easier to print and assemble, and so that the cable cannot easily be pulled loose. The mechanism, the board, the wiring inside and every pin-to-pin length are unchanged, so the 60 mm arm still fits.

- **Cable clamp:**
  - **Exit:** the two cable wires now leave sideways on the board side, inside a 3 mm sleeve (silicone or PVC tube, 2 mm bore).
  - **New part:** the printed `06_cable_clamp` plate sits in a pocket in the rear cap.
  - **Grip:** the two rear-cap screws (M2 × 10 then, M1 × 8 into inserts since 11 November) pass through the plate and press it onto the sleeve. The groove is 2.6 mm high with three ridges, so the sleeve is squeezed by 0.4 mm. The groove's mouth is flared so the cable bends gently instead of over an edge.
  - **Wires:** a knot in each wire stops it at the cap's wire slot.
  - **Result:** a pull on the cable is taken by the clamp and the knots, not by the solder joints. The two loose 28 AWG wires through 1.2 mm holes are gone.
- **Body printed rear end down** (front end down since 11 November, for the rear-cap hook):
  - The rear locating rim is gone, so the body stands on a flat face.
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
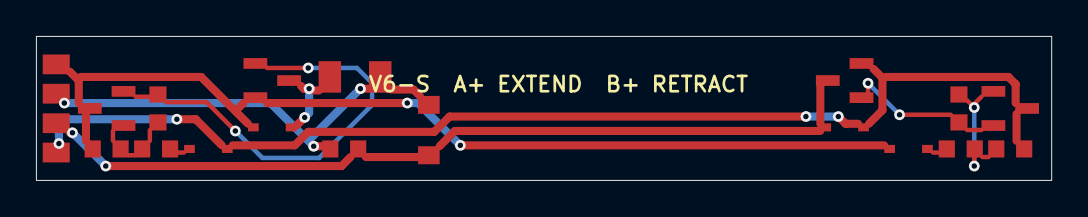
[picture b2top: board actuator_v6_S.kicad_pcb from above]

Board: 2 copper layers, 56.4 x 8.0 mm, 21 parts (0 on the bottom side), 11 nets.

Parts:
C1, C2: 1 µF 50 V X5R; C_0603_1608Metric
C3: 100 nF 50 V X7R; C_0603_1608Metric
D1, D2: 1N4148WS; D_SOD-323
D3: SMF15CA; D_SOD-123F
D4, D5: B5819WS; D_SOD-323
F1: 0.35 A PPTC; Fuse_1206_3216Metric
J_A: cable wire A (+ = extend); WirePad_1.1x1.5
J_B: cable wire B (+ = retract); WirePad_1.1x1.5
J_M+: to motor terminal +; WirePad_1.1x1.5
J_M-: to motor terminal -; WirePad_1.1x1.5
Q1, Q2: IRLML0060TRPBF; SOT-23
R1, R2: 1 MΩ 1 %; R_0603_1608Metric
R3, R4: 220 Ω 1 %; R_0603_1608Metric
U1, U2: DRV5033AJQDBZR; SOT-23

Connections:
A: C1.2, D2.2, D4.2, J_A.1, Q1.2, U1.3
A_SW: D4.1, F1.1, Q1.3
B: C2.2, D1.2, D5.2, J_B.1, Q2.2, U2.3
G_EXT: Q2.1, R2.2, U2.2
G_RET: Q1.1, R1.2, U1.2
MOT+: C3.1, D3.1, F1.2, J_M+.1
MOT-: C3.2, D3.2, D5.1, J_M-.1, Q2.3
VCC_EXT: C2.1, R2.1, R4.2, U2.1
VCC_RET: C1.1, R1.1, R3.2, U1.1
VD_EXT: D2.1, R4.1
VD_RET: D1.1, R3.1

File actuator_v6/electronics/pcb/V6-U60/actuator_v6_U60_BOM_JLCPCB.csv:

Comment,Designator,Footprint,LCSC Part #,Manufacturer part,Quantity
1 µF 50 V X5R,"C1,C2",C_0603_1608Metric,C15849,Samsung CL10A105KB8NNNC,2
100 nF 50 V X7R,C3,C_0603_1608Metric,C14663,Yageo CC0603KRX7R9BB104,1
1N4148WS,"D1,D2",D_SOD-323,C2128,JSCJ 1N4148WS,2
SMF15CA,D3,D_SOD-123F,C123803,MDD SMF15CA (bidirectional),1
B5819WS,"D4,D5",D_SOD-323,C22624,JSCJ B5819WS,2
0.35 A PPTC,F1,Fuse_1206_3216Metric,C208468,Bourns MF-NSMF035X-2,1
IRLML0060TRPBF,"Q1,Q2",SOT-23,C67274,Infineon IRLML0060TRPBF,2
1 MΩ 1 %,"R1,R2",R_0603_1608Metric,C22935,UNI-ROYAL 0603WAF1004T5E,2
220 Ω 1 %,"R3,R4",R_0603_1608Metric,C22962,UNI-ROYAL 0603WAF2200T5E,2
DRV5033AJQDBZR,"U1,U2",SOT-23,C85151,TI DRV5033AJQDBZR,2

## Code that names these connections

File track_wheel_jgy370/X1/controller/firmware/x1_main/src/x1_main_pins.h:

// X1 main board rev B: GPIO map. Generated by main_board/source/pinmap.py from netlist.py;
// do not edit by hand.
#pragma once

namespace x1pins {

constexpr int BOOT = 0;  // input: BOOT button (strap); usable as a user button after boot
constexpr int ISNS_TL = 1;  // ADC1_CH0: Track left: current, 2400 ohm x 1000 uA/A; 1.034 A limit = 2.481 V
constexpr int ISNS_TR = 2;  // ADC1_CH1: Track right: current, 2400 ohm x 1000 uA/A; 1.034 A limit = 2.481 V
constexpr int ISNS_ST = 3;  // ADC1_CH2: Stick: current, 4990 ohm x 1000 uA/A; 0.497 A limit = 2.481 V
constexpr int BUZ_PWM = 4;  // LEDC: buzzer, PWM at about 2.7 kHz
constexpr int ISNS_SW = 5;  // ADC1_CH4: Swing: current, 4120 ohm x 1000 uA/A; 0.602 A limit = 2.481 V
constexpr int ISNS_BK = 6;  // ADC1_CH5: Bucket: current, 4990 ohm x 1000 uA/A; 0.497 A limit = 2.481 V
constexpr int VBAT_SNS = 8;  // ADC1_CH7: battery voltage x 22k/122k
constexpr int ISNS_BR = 9;  // ADC1_CH8: Boom right: current, 4990 ohm x 1000 uA/A; 0.497 A limit = 2.481 V
constexpr int ISNS_BL = 10;  // ADC1_CH9: Boom left: current, 4990 ohm x 1000 uA/A; 0.497 A limit = 2.481 V
constexpr int EN_ST = 11;  // PWM (MCPWM): Stick: speed, 0 = brake
constexpr int PH_ST = 12;  // output: Stick: direction, 1 = OUT1 high
constexpr int EN_BR = 13;  // PWM (MCPWM): Boom right: speed, 0 = brake
constexpr int PH_BR = 14;  // output: Boom right: direction, 1 = OUT1 high
constexpr int EN_SW = 15;  // PWM (MCPWM): Swing: speed, 0 = brake
constexpr int PH_SW = 16;  // output: Swing: direction, 1 = OUT1 high
constexpr int EN_BK = 17;  // PWM (MCPWM): Bucket: speed, 0 = brake
constexpr int PH_BK = 18;  // output: Bucket: direction, 1 = OUT1 high
constexpr int USB_DN = 19;  // USB: native USB D-
constexpr int USB_DP = 20;  // USB: native USB D+
constexpr int EN_BL = 21;  // PWM (MCPWM): Boom left: speed, 0 = brake
constexpr int EN_TL = 35;  // PWM (MCPWM): Track left: speed, 0 = brake
constexpr int PH_TL = 36;  // output: Track left: direction, 1 = OUT1 high
constexpr int EN_TR = 37;  // PWM (MCPWM): Track right: speed, 0 = brake
constexpr int PH_TR = 38;  // output: Track right: direction, 1 = OUT1 high
constexpr int NFAULT = 39;  // input: any driver fault, open drain, 10k pull-up; low = fault
constexpr int LED_STAT = 40;  // output: status LED, high = on
constexpr int EXP_TX = 41;  // UART1 TX: expansion header pin 3 (through 100R)
constexpr int EXP_RX = 42;  // UART1 RX: expansion header pin 4 (through 1k)
constexpr int TXD0 = 43;  // UART0 TX: boot log, test pad TP201
constexpr int RXD0 = 44;  // UART0 RX: test pad TP202
constexpr int LAMP1_PWM = 45;  // LEDC: lamp 1 low-side switch; strap pin, 100k pull-down
constexpr int LAMP2_PWM = 46;  // LEDC: lamp 2 low-side switch; strap pin, 100k pull-down
constexpr int PH_BL = 47;  // output: Boom left: direction, 1 = OUT1 high
constexpr int NSLEEP = 48;  // output: all seven drivers: 1 = awake (armed), 0 = sleep; 100k pull-down

struct Channel { const char *name; int en, ph, isns; float r_ipropi_ohm; float limit_a; };
constexpr Channel CHANNELS[] = {
    {"Track left", 35, 36, 1, 2400.0f, 1.0338f},
    {"Track right", 37, 38, 2, 2400.0f, 1.0338f},
    {"Swing", 15, 16, 5, 4120.0f, 0.6022f},
    {"Boom left", 21, 47, 10, 4990.0f, 0.4972f},
    {"Boom right", 13, 14, 9, 4990.0f, 0.4972f},
    {"Stick", 11, 12, 3, 4990.0f, 0.4972f},
    {"Bucket", 17, 18, 6, 4990.0f, 0.4972f},
};
constexpr float VREF_V = 2.4812f;
constexpr float VBAT_DIVIDER = 0.18033f;  // V_adc = VBAT x this

}  // namespace x1pins
